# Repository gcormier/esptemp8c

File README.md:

# esptemp8c

Open source, n-channel temperature logger using esphome for Dallas DS18B20 sensors. Powered by an ESP32-C3-MINI, it can be powered by USB-C or by 24VAC.

## Sensors
They can be found at various locations, including [DFRobot](https://www.dfrobot.com/product-689.html), [Adafruit](https://www.adafruit.com/product/381), Digikey or the usual suspects.

You will need to find out your sensor ID's as per the [esphome documentation](https://esphome.io/components/one_wire#one-wire).

### Counterfeit Sensors
If you are using a Dallas DS18B20 sensor, I strongly recommend using Digikey, Mouser or Adafruit to avoid obtaining [counterfeit sensors](https://github.com/cpetrich/counterfeit_DS18B20/tree/master).

## Powering
Only *one* power source should be used.
- USB-C Jack (5V)
- Screw terminal
    - It is designed for 24VAC. 12VAC is probably the minimum required for AC. Do not exceed 24VAC.
    - 9VDC will be the minimum required amount if using DC, and it has been tested up to 24VDC. 

A self-resetting polyfuse is included to protect HVAC equipment if sourcing 24VAC from these units. The polyfuse does NOT apply to power from the USB-C port, as the device supplying power should have overcurrent protection per the USB standard.

## Flashing / Programming
You must hold down the button while plugging in the device the first time to enter programming mode. The device will then show up as a USB device on your computer. You can then use the esphome flasher to flash the device.

Subsequent flashing does not require use of the button - it can be done via USBC or OTA as well.

## Enclosure
Fits in a [Hammond 1593KBK](https://www.hammfg.com/part/1593KBK). Or you can make your own enclosure and 3D-print it (contributions welcome).

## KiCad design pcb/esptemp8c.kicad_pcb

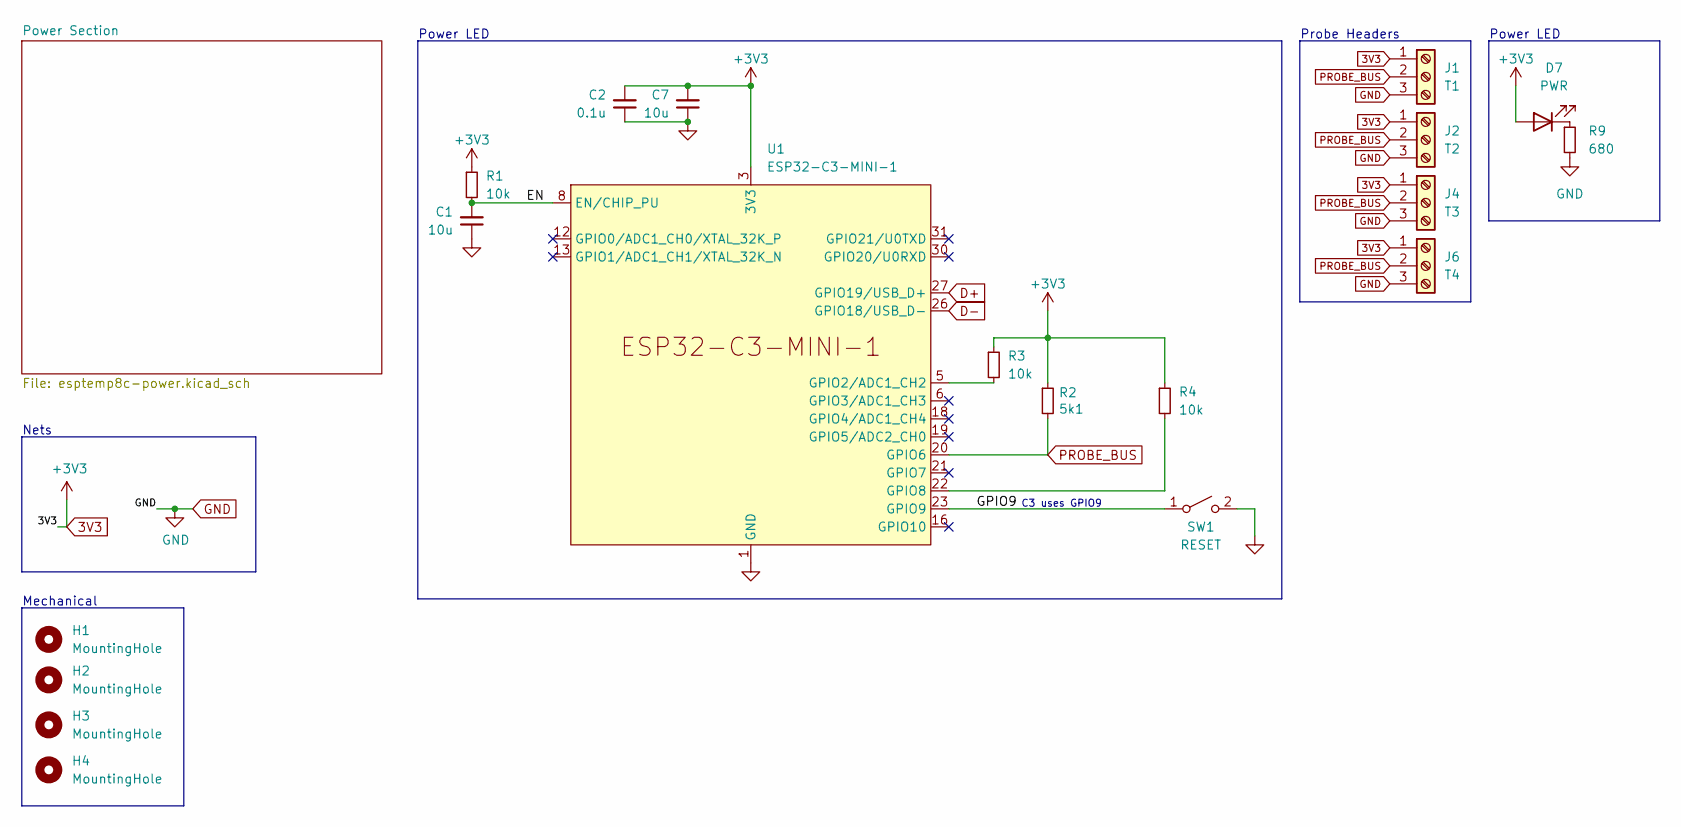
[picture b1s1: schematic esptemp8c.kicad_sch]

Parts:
C1, C7: 10u; C_0805_2012Metric; LCSC C15850
C2: 0.1u; C_0603_1608Metric; LCSC C14663
D7: PWR; LED_0805_2012Metric; LCSC C84256
H1, H2, H3, H4: MountingHole; MountingHole_3.2mm_M3
J1: T1; PhoenixContact_MC_1,5_3-G-3.81_1x03_P3.81mm_Horizontal; LCSC C8406
J2: T2; PhoenixContact_MC_1,5_3-G-3.81_1x03_P3.81mm_Horizontal; LCSC C8406
J4: T3; PhoenixContact_MC_1,5_3-G-3.81_1x03_P3.81mm_Horizontal; LCSC C8406
J6: T4; PhoenixContact_MC_1,5_3-G-3.81_1x03_P3.81mm_Horizontal; LCSC C8406
R1, R3, R4: 10k; R_0402_1005Metric; LCSC C25744
R2: 5k1; R_0402_1005Metric; LCSC C25905
R9: 680; R_0402_1005Metric; LCSC C25130
SW1: RESET; SW_Push_1P1T_XKB_TS-1187A; LCSC C318884
U1: ESP32-C3-MINI-1; LCSC C2838502

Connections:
3V3: C2.2, C7.2, D7.2 (A), J1.1, J2.1, J4.1, J6.1, R1.1, R2.1, R3.1, R4.1, U1.3 (3V3); also elsewhere on the board
/EN: C1.2, R1.2, U1.8 (EN/CHIP_PU)
/GPIO9: SW1.1 (A), U1.23 (GPIO9)
D+: U1.27 (GPIO19/USB_D+); also elsewhere on the board
D-: U1.26 (GPIO18/USB_D-); also elsewhere on the board
GND: C1.1, C2.1, C7.1, J1.3, J2.3, J4.3, J6.3, R9.2, SW1.2 (B), U1.1 (GND), U1.2 (GND), U1.11 (GND), U1.14 (GND), U1.36 (GND), U1.37 (GND), U1.38 (GND), U1.39 (GND), U1.40 (GND), U1.41 (GND), U1.42 (GND), U1.43 (GND), U1.44 (GND), U1.45 (GND), U1.46 (GND), U1.47 (GND), U1.48 (GND), U1.49 (GND), U1.50 (GND), U1.51 (GND), U1.52 (GND), U1.53 (GND); also elsewhere on the board
unnamed: D7.1 (K), R9.1
unnamed: R3.2, U1.5 (GPIO2/ADC1_CH2)
unnamed: R4.2, U1.22 (GPIO8)
PROBE_BUS: J1.2, J2.2, J4.2, J6.2, R2.2, U1.20 (GPIO6)

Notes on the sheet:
Nets
C3 uses GPIO9
Mechanical
Probe Headers
Power LED

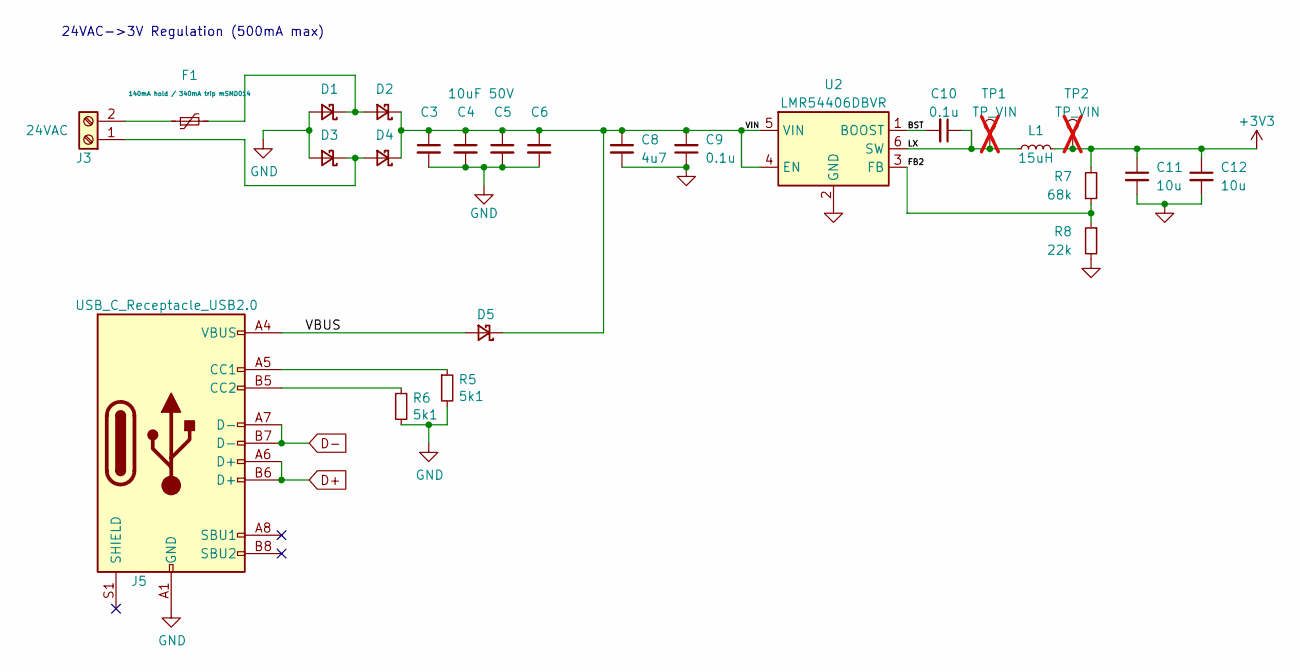
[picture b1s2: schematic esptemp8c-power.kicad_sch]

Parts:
C3, C4, C5, C6: 10uF 50V; C_1206_3216Metric; LCSC C13585
C8: 4u7; C_1206_3216Metric; LCSC C29823
C9, C10: 0.1u; C_0603_1608Metric; LCSC C14663
C11, C12: 10u; C_0805_2012Metric; LCSC C15850
D1, D2, D3, D4, D5: 1N5819WS; D_SOD-323; LCSC C191023
F1: 140mA hold / 340mA trip mSMD014; Fuse_1812_4532Metric; LCSC C70106
J3: 24VAC; PhoenixContact_MC_1,5_2-G-3.81_1x02_P3.81mm_Horizontal; LCSC C480537
J5: USB_C_Receptacle_USB2.0; USB_C_Receptacle_HRO_TYPE-C-31-M-12; LCSC C165948
L1: 15uH; L_Sunlord_SWPA6028S; LCSC C83373
R5, R6: 5k1; R_0402_1005Metric; LCSC C25905
R7: 68k; R_0402_1005Metric; LCSC C36871
R8: 22k; R_0402_1005Metric; LCSC C25768
TP1, TP2: TP_VIN; PinHeader_1x01_P2.54mm_Vertical; not fitted
U2: LMR54406DBVR; SOT-23-6; LCSC C5219316

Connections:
3V3: C11.1, C12.1, L1.2, R7.2, TP2.1; also elsewhere on the board
/Power Section/BST: C10.2, U2.1 (BOOST)
/Power Section/FB2: R7.1, R8.1, U2.3 (FB)
/Power Section/LX: C10.1, L1.1, TP1.1, U2.6 (SW)
/Power Section/VBUS: D5.2 (A), J5.A4 (VBUS), J5.A9 (VBUS), J5.B4 (VBUS), J5.B9 (VBUS)
/Power Section/VIN: C3.1, C4.1, C5.1, C6.1, C8.1, C9.2, D2.1 (K), D4.1 (K), D5.1 (K), U2.4 (EN), U2.5 (VIN)
D+: J5.A6 (D+), J5.B6 (D+); also elsewhere on the board
D-: J5.A7 (D-), J5.B7 (D-); also elsewhere on the board
GND: C3.2, C4.2, C5.2, C6.2, C8.2, C9.1, C11.2, C12.2, D1.2 (A), D3.2 (A), J5.A1 (GND), J5.A12 (GND), J5.B1 (GND), J5.B12 (GND), R5.2, R6.2, R8.2, U2.2 (GND); also elsewhere on the board
unnamed: D1.1 (K), D2.2 (A), F1.2
unnamed: D3.1 (K), D4.2 (A), J3.1
unnamed: F1.1, J3.2
unnamed: J5.A5 (CC1), R5.1
unnamed: J5.B5 (CC2), R6.1

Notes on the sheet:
24VAC->3V Regulation (500mA max)

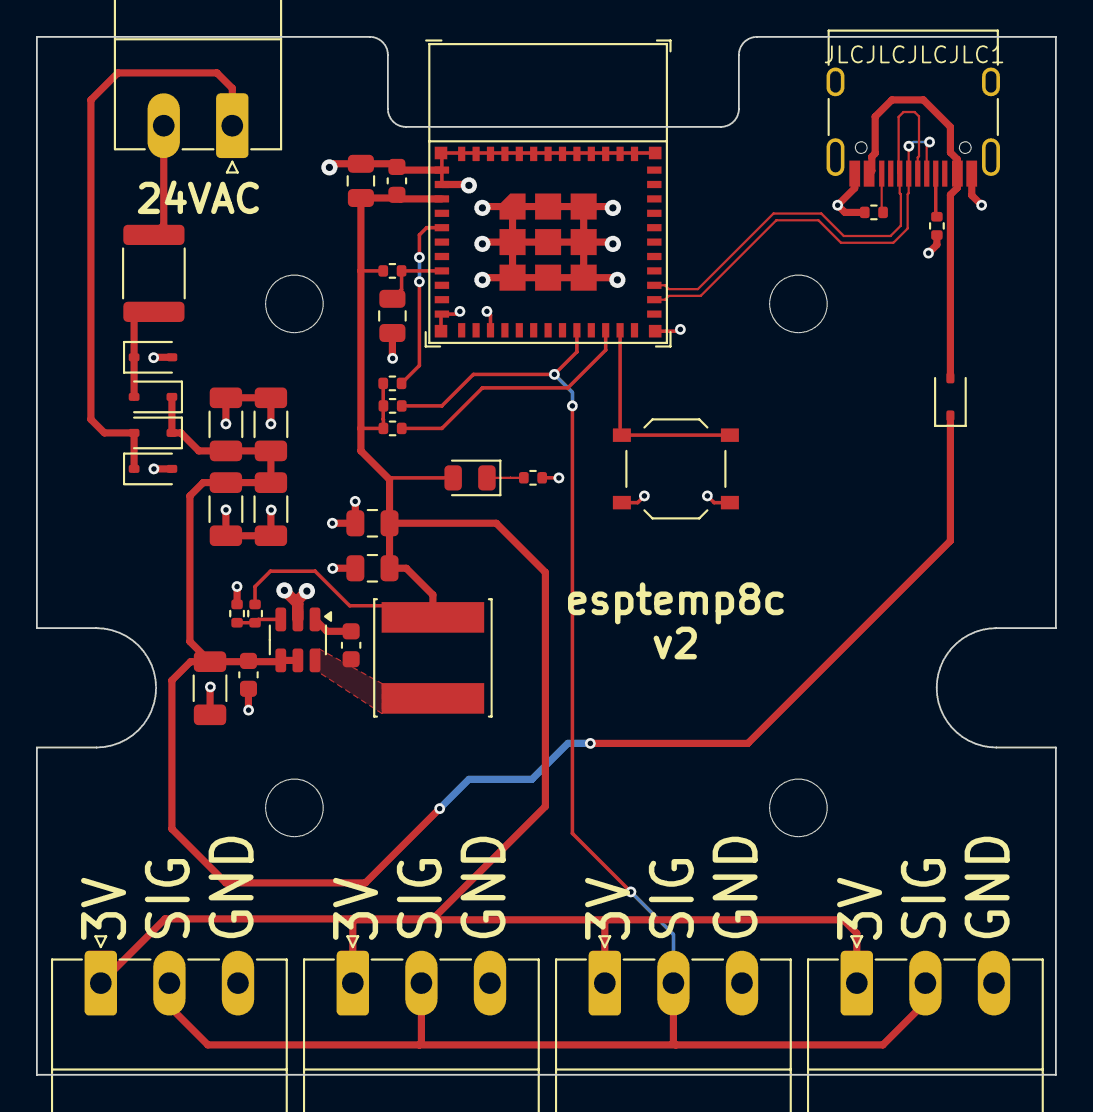
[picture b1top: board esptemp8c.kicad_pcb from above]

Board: 2 copper layers, 56.6 x 57.7 mm, 42 parts (0 on the bottom side), 20 nets.

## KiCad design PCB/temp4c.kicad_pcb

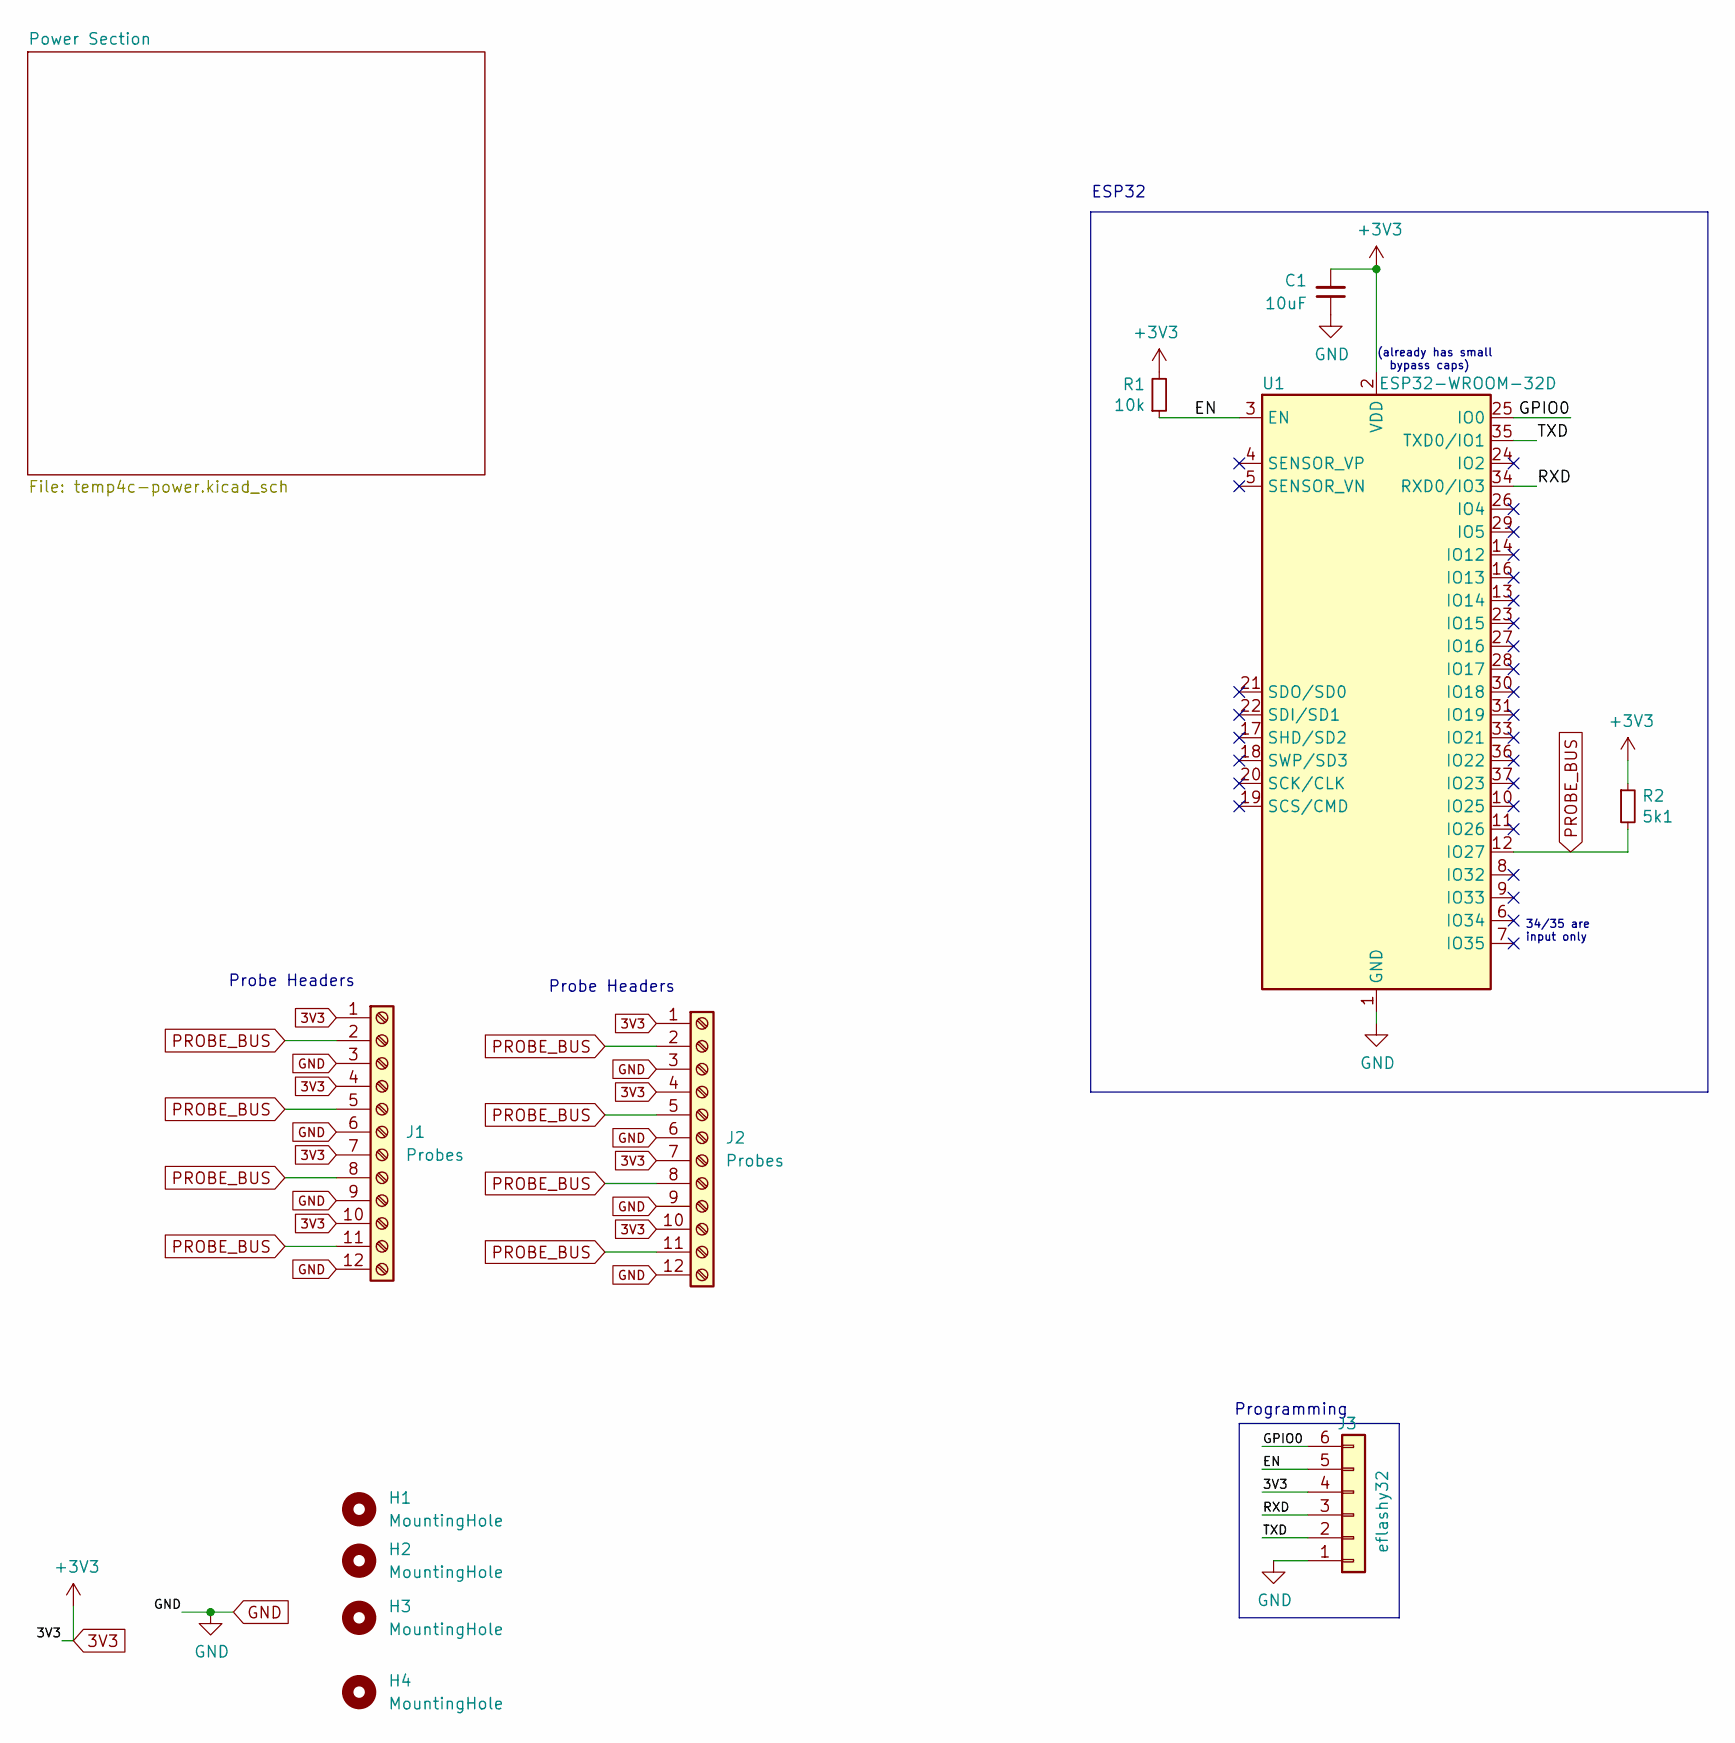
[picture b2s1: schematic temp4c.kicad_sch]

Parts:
C1: 10uF; C_0805_2012Metric; LCSC C15850
H1, H2, H3, H4: MountingHole; MountingHole_3.2mm_M3
J1, J2: Probes; TerminalBlock_Phoenix_MPT-0,5-12-2.54_1x12_P2.54mm_Horizont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
J3: eflashy32; PinHeader_1x06_P2.54mm_Vertical; LCSC DNP
R1: 10k; R_0402_1005Metric; LCSC C25744
R2: 5k1; R_0402_1005Metric; LCSC C25905
U1: ESP32-WROOM-32D; ESP32-WROOM-32; LCSC C701342

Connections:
3V3: C1.2, J1.1, J1.4, J1.7, J1.10, J2.1, J2.4, J2.7, J2.10, J3.4, R1.2, R2.1, U1.2 (VDD); also elsewhere on the board
/EN: J3.5, R1.1, U1.3 (EN)
/GPIO0: J3.6, U1.25 (IO0)
/RXD: J3.3, U1.34 (RXD0/IO3)
/TXD: J3.2, U1.35 (TXD0/IO1)
GND: C1.1, J1.3, J1.6, J1.9, J1.12, J2.3, J2.6, J2.9, J2.12, J3.1, U1.1 (GND), U1.15 (GND), U1.38 (GND), U1.39 (GND); also elsewhere on the board
PROBE_BUS: J1.2, J1.5, J1.8, J1.11, J2.2, J2.5, J2.8, J2.11, R2.2, U1.12 (IO27)

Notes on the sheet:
34/35 are input only
ESP32
Probe Headers
(already has small bypass caps)
Programming

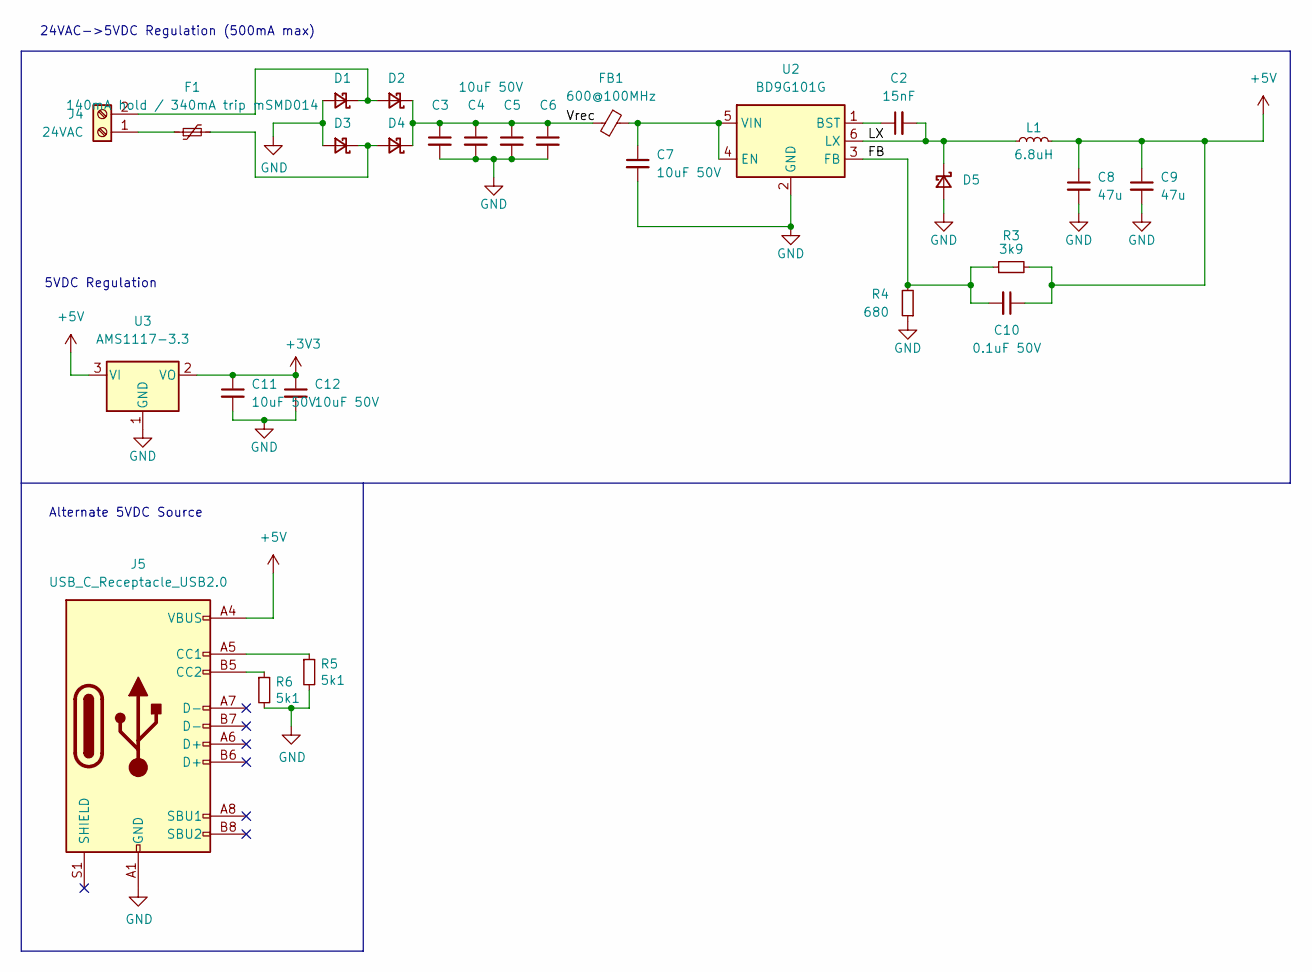
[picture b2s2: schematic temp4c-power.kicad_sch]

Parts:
C2: 15nF; C_0603_1608Metric; LCSC C1596
C3, C4, C5, C6, C7, C11, C12: 10uF 50V; C_1206_3216Metric; LCSC C13585
C8, C9: 47u; C_1206_3216Metric; LCSC C96123
C10: 0.1uF 50V; C_0603_1608Metric; LCSC C14663
D1, D2, D3, D4, D5: SS210; D_SMA; LCSC C14996
F1: 140mA hold / 340mA trip mSMD014; Fuse_1812_4532Metric; LCSC C70106
FB1: 600@100MHz; L_0805_2012Metric; LCSC C1017
J4: 24VAC; TerminalBlock_Phoenix_MKDS-1,5-2-5.08_1x02_P5.08mm_Horizont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; Part 1935161; LCSC DNP
J5: USB_C_Receptacle_USB2.0; USB_C_Receptacle_HRO_TYPE-C-31-M-12; LCSC C165948
L1: 6.8uH; L_Sunlord_SWPA60xxS; LCSC C57254
R3: 3k9; R_0402_1005Metric; LCSC C51721
R4: 680; R_0402_1005Metric; LCSC C25130
R5, R6: 5k1; R_0402_1005Metric; LCSC C25905
U2: BD9G101G; SOT-23-6; LCSC C108761
U3: AMS1117-3.3; SOT-223-3_TabPin2; LCSC C6186

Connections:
3V3: C11.1, C12.1, U3.2 (VO); also elsewhere on the board
+5V: C8.1, C9.1, C10.1, J5.A4 (VBUS), J5.A9 (VBUS), J5.B4 (VBUS), J5.B9 (VBUS), L1.2, R3.2, U3.3 (VI)
/Power Section/FB: C10.2, R3.1, R4.2, U2.3 (FB)
/Power Section/LX: C2.2, D5.1 (K), L1.1, U2.6 (LX)
/Power Section/Vrec: C3.1, C4.1, C5.1, C6.1, D2.1 (K), D4.1 (K), FB1.2
GND: C3.2, C4.2, C5.2, C6.2, C7.2, C8.2, C9.2, C11.2, C12.2, D1.2 (A), D3.2 (A), D5.2 (A), J5.A1 (GND), J5.A12 (GND), J5.B1 (GND), J5.B12 (GND), R4.1, R5.2, R6.2, U2.2 (GND), U3.1 (GND); also elsewhere on the board
unnamed: C2.1, U2.1 (BST)
unnamed: C7.1, FB1.1, U2.4 (EN), U2.5 (VIN)
unnamed: D1.1 (K), D2.2 (A), J4.2
unnamed: D3.1 (K), D4.2 (A), F1.2
unnamed: F1.1, J4.1
unnamed: J5.A5 (CC1), R5.1
unnamed: J5.B5 (CC2), R6.1

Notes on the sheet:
5VDC Regulation
Alternate 5VDC Source
24VAC->5VDC Regulation (500mA max)

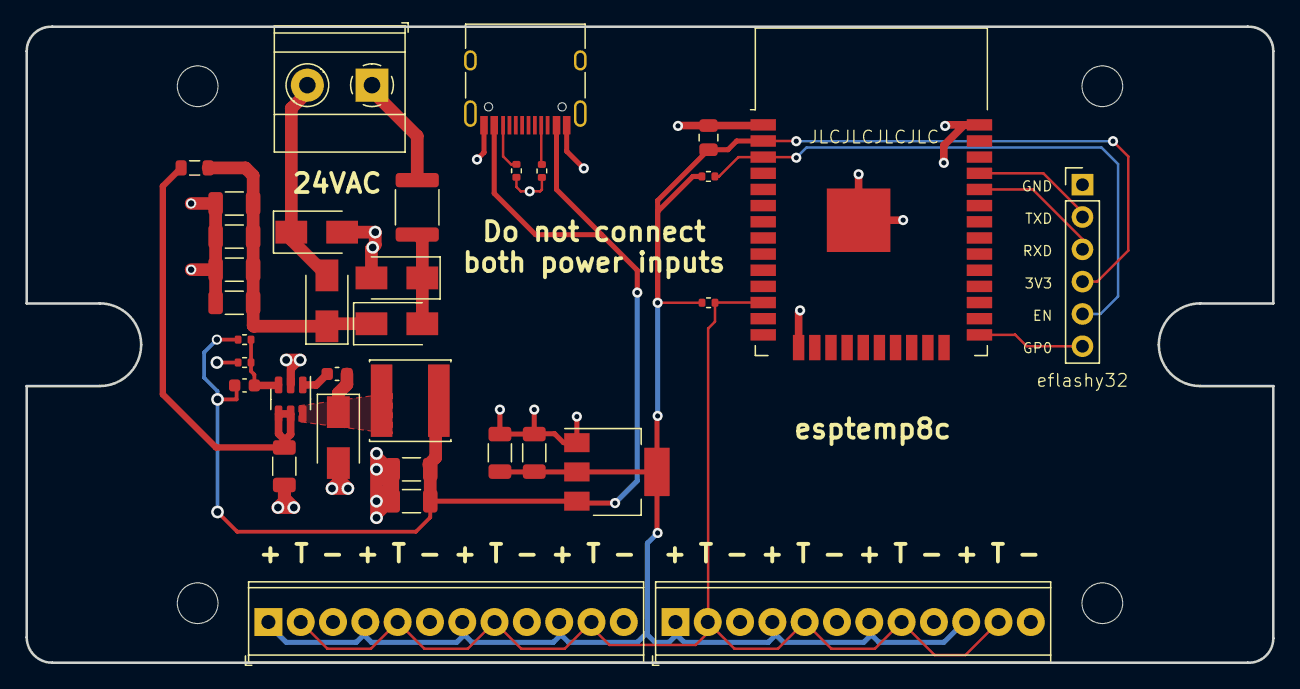
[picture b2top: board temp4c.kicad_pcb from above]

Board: 2 copper layers, 98.0 x 50.0 mm, 38 parts (0 on the bottom side), 18 nets.

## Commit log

2022-08-20 pipelines
2022-08-20 order number silkscreen
2022-08-20 lcsc PN for esp32
2022-08-21 switch rectifier
2022-08-21 include THT
2022-08-21 try aux axis setting?
2022-08-21 rotation
2022-08-21 esp32 custom rot
2022-08-21 esp32rot2
2022-08-21 Tidy/labels
2022-12-04 esptemp8c rename
2022-12-04 fix ground pin on eflashy32
2022-12-04 silkscreen for eflashy32
2022-12-13 rename
2022-12-13 fix case
2022-12-13 docs
2022-12-13 resize
2022-12-14 name, images, link
2022-12-14 image
2022-12-21 build update
2022-12-21 inner
2022-12-21 render
2023-02-05 include simple REST example
2024-08-01 updates for v2
2024-08-01 more v2 changes
2024-08-01 actions
2024-08-01 zoom
2024-08-01 fix rounding
2024-08-01 edgecuts
2024-08-01 moar
2024-08-01 moard
2024-08-01 proper panel space
2024-08-01 docs and pics
2024-08-01 update render
2024-08-01 fix footprint to sot23
2024-08-01 final touches and check
2024-08-01 panel of 2 only
2024-08-02 rorate
2024-08-02 unrorate
2024-08-02 add panels
2024-08-02 panel touchup, alternate pn
2024-09-25 update yaml for c3
2024-09-25 ignore secrets
